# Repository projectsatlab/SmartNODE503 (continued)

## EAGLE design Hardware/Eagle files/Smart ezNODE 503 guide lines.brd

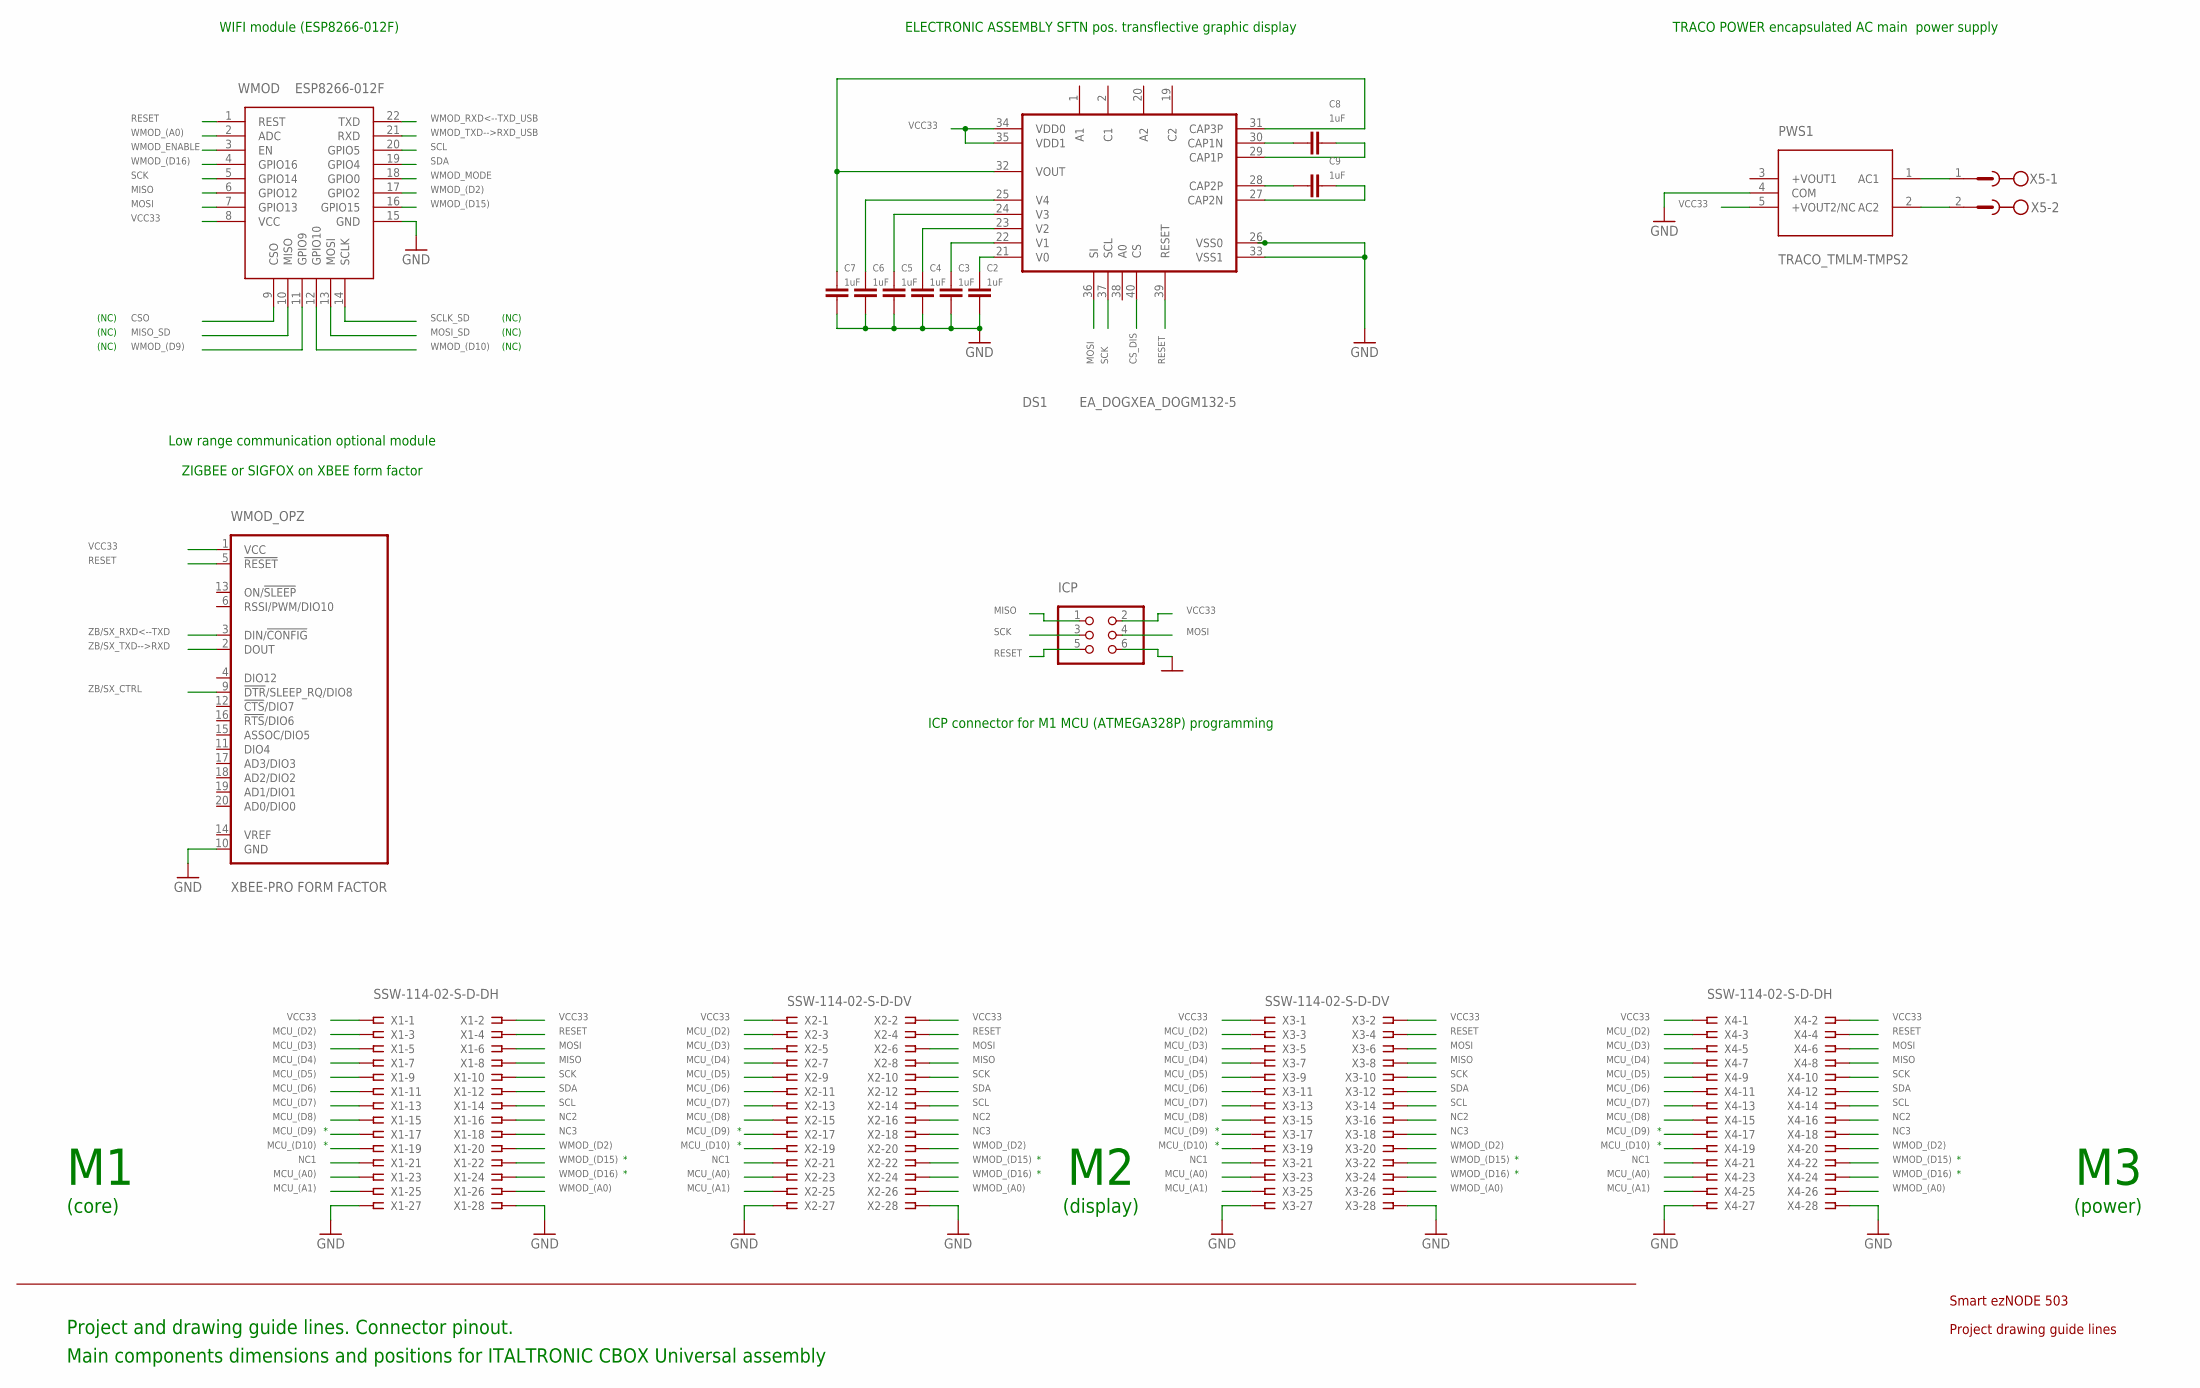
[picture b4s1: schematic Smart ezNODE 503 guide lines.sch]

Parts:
C2, C3, C4, C5, C6, C7, C8, C9: 1uF; C0402
DS1: EA_DOGXEA_DOGM132-5; EA_DOGM
ICP: PINHD-2X3/SMD; 2X3_SMD
PWS1: TRACO_TMLM-TMPS2; TRACO_TMPS03XXX
WMOD: ESP8266-012F; ESP8266-ESP12
WMOD_OPZ: XBEE-PRO FORM FACTOR; XBEE-PRO
X1, X4: SSW-114-02-S-D-DH; FTE-114-XX-G-DH
X2, X3: SSW-114-02-S-D-DV; CLE-114-01-X-DV-A
X5: MSTBV2

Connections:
CSO: WMOD.9 (CSO)
CS_DIS: DS1.40 (CS)
GND: C2.2, C3.2, C4.2, C5.2, C6.2, C7.2, DS1.26 (VSS0), DS1.33 (VSS1), ICP.6, PWS1.4 (COM), WMOD.15 (GND), WMOD_OPZ.10 (GND), X1.27, X1.28, X2.27, X2.28, X3.27, X3.28, X4.27, X4.28
MCU_(A0): X1.23, X2.23, X3.23, X4.23
MCU_(A1): X1.25, X2.25, X3.25, X4.25
MCU_(D2): X1.3, X2.3, X3.3, X4.3
MCU_(D3): X1.5, X2.5, X3.5, X4.5
MCU_(D4): X1.7, X2.7, X3.7, X4.7
MCU_(D5): X1.9, X2.9, X3.9, X4.9
MCU_(D6): X1.11, X2.11, X3.11, X4.11
MCU_(D7): X1.13, X2.13, X3.13, X4.13
MCU_(D8): X1.15, X2.15, X3.15, X4.15
MCU_(D9): X1.17, X2.17, X3.17, X4.17
MCU_(D10): X1.19, X2.19, X3.19, X4.19
MISO: ICP.1, WMOD.6 (GPIO12), X1.8, X2.8, X3.8, X4.8
MISO_SD: WMOD.10 (MISO)
MOSI: DS1.36 (SI), ICP.4, WMOD.7 (GPIO13), X1.6, X2.6, X3.6, X4.6
MOSI_SD: WMOD.13 (MOSI)
unnamed: PWS1.1 (AC1), X5.1
unnamed: PWS1.2 (AC2), X5.2
unnamed: C2.1, DS1.21 (V0)
unnamed: C8.1, DS1.30 (CAP1N)
unnamed: C3.1, DS1.22 (V1)
unnamed: C4.1, DS1.23 (V2)
unnamed: C5.1, DS1.24 (V3)
unnamed: C6.1, DS1.25 (V4)
unnamed: C7.1, DS1.31 (CAP3P), DS1.32 (VOUT)
unnamed: C8.2, DS1.29 (CAP1P)
unnamed: C9.1, DS1.28 (CAP2P)
unnamed: C9.2, DS1.27 (CAP2N)
NC1: X1.21, X2.21, X3.21, X4.21
NC2: X1.16, X2.16, X3.16, X4.16
NC3: X1.18, X2.18, X3.18, X4.18
RESET: DS1.39 (RESET), ICP.5, WMOD.1 (REST), WMOD_OPZ.5 (!RESET), X1.4, X2.4, X3.4, X4.4
SCK: DS1.37 (SCL), ICP.3, WMOD.5 (GPIO14), X1.10, X2.10, X3.10, X4.10
SCL: WMOD.20 (GPIO5), X1.14, X2.14, X3.14, X4.14
SCLK_SD: WMOD.14 (SCLK)
SDA: WMOD.19 (GPIO4), X1.12, X2.12, X3.12, X4.12
VCC33: DS1.34 (VDD0), DS1.35 (VDD1), ICP.2, WMOD.8 (VCC), WMOD_OPZ.1 (VCC), X1.1, X1.2, X2.1, X2.2, X3.1, X3.2, X4.1, X4.2
WMOD_(A0): WMOD.2 (ADC), X1.26, X2.26, X3.26, X4.26
WMOD_(D2): WMOD.17 (GPIO2), X1.20, X2.20, X3.20, X4.20
WMOD_(D9): WMOD.11 (GPIO9)
WMOD_(D10): WMOD.12 (GPIO10)
WMOD_(D15): WMOD.16 (GPIO15), X1.22, X2.22, X3.22, X4.22
WMOD_(D16): WMOD.4 (GPIO16), X1.24, X2.24, X3.24, X4.24
WMOD_ENABLE: WMOD.3 (EN)
WMOD_MODE: WMOD.18 (GPIO0)
WMOD_RXD<--TXD_USB: WMOD.22 (TXD)
WMOD_TXD-->RXD_USB: WMOD.21 (RXD)
ZB/SX_RXD<--TXD: WMOD_OPZ.3 (DIN/!CONFIG)
ZB/SX_TXD-->RXD: WMOD_OPZ.2 (DOUT)

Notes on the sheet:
WIFI module (ESP8266-012F)
Low range communication optional module ZIGBEE or SIGFOX on XBEE form factor
Smart ezNODE 503
Project drawing guide lines
(core)
(display)
(power)
Project and drawing guide lines. Connector pinout.
Main components dimensions and positions for ITALTRONIC CBOX Universal assembly
ELECTRONIC ASSEMBLY SFTN pos. transflective graphic display
TRACO POWER encapsulated AC main power supply
ICP connector for M1 MCU (ATMEGA328P) programming
(NC)

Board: 2 copper layers, 18 parts (16 on the bottom side), 38 nets, no tracks yet.

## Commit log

2016-11-23 Create LICENCE
